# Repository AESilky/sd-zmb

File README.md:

# Silky Design & CMOS1 - Z80 Retro Motherboard

This is a Z80-based 'retro-style' Single Board Computer (motherboard).

The motherboard includes enough to run stand-alone.
That includes:

1. Z80 CPU
2. Selectable CPU clock frequencies
3. Reset circuit, divided into a POR board/system reset and a Z80/CPU only reset
4. Memory Management Unit (MMU) that provides bank selecting 8 of 64 8K banks (2M physical address)
5. 512K bytes RAM and 512K bytes Flash ROM
6. 2 Serial ports. One with USB 'device' interface, one with USB host interface (KBD)
7. RP2040 module to provide USB Host (for a keyboard) and an SD Card interface. The SD Card can be used for:
   a. EEPROM (like) configuration storage
   b. Virtual IDE drive(s)
   c. Raw SD Card access
   d. Multicolor LED indicator (via the onboard NeoPixel)
8. Programmable BAUD rate generator
9. Periodic interrupt generated by 3rd CTC channel
10. OLED or TFT graphics display (can be used for graphics or multi-line text)
11. RC2014-80 Extended/Enhanced Bus

The design started with much more on the board, but has been paired down to make the size and complexity of the board more reasonable. The 'features' that have been removed have been moved into projects of their own to be built-out as expansion boards.

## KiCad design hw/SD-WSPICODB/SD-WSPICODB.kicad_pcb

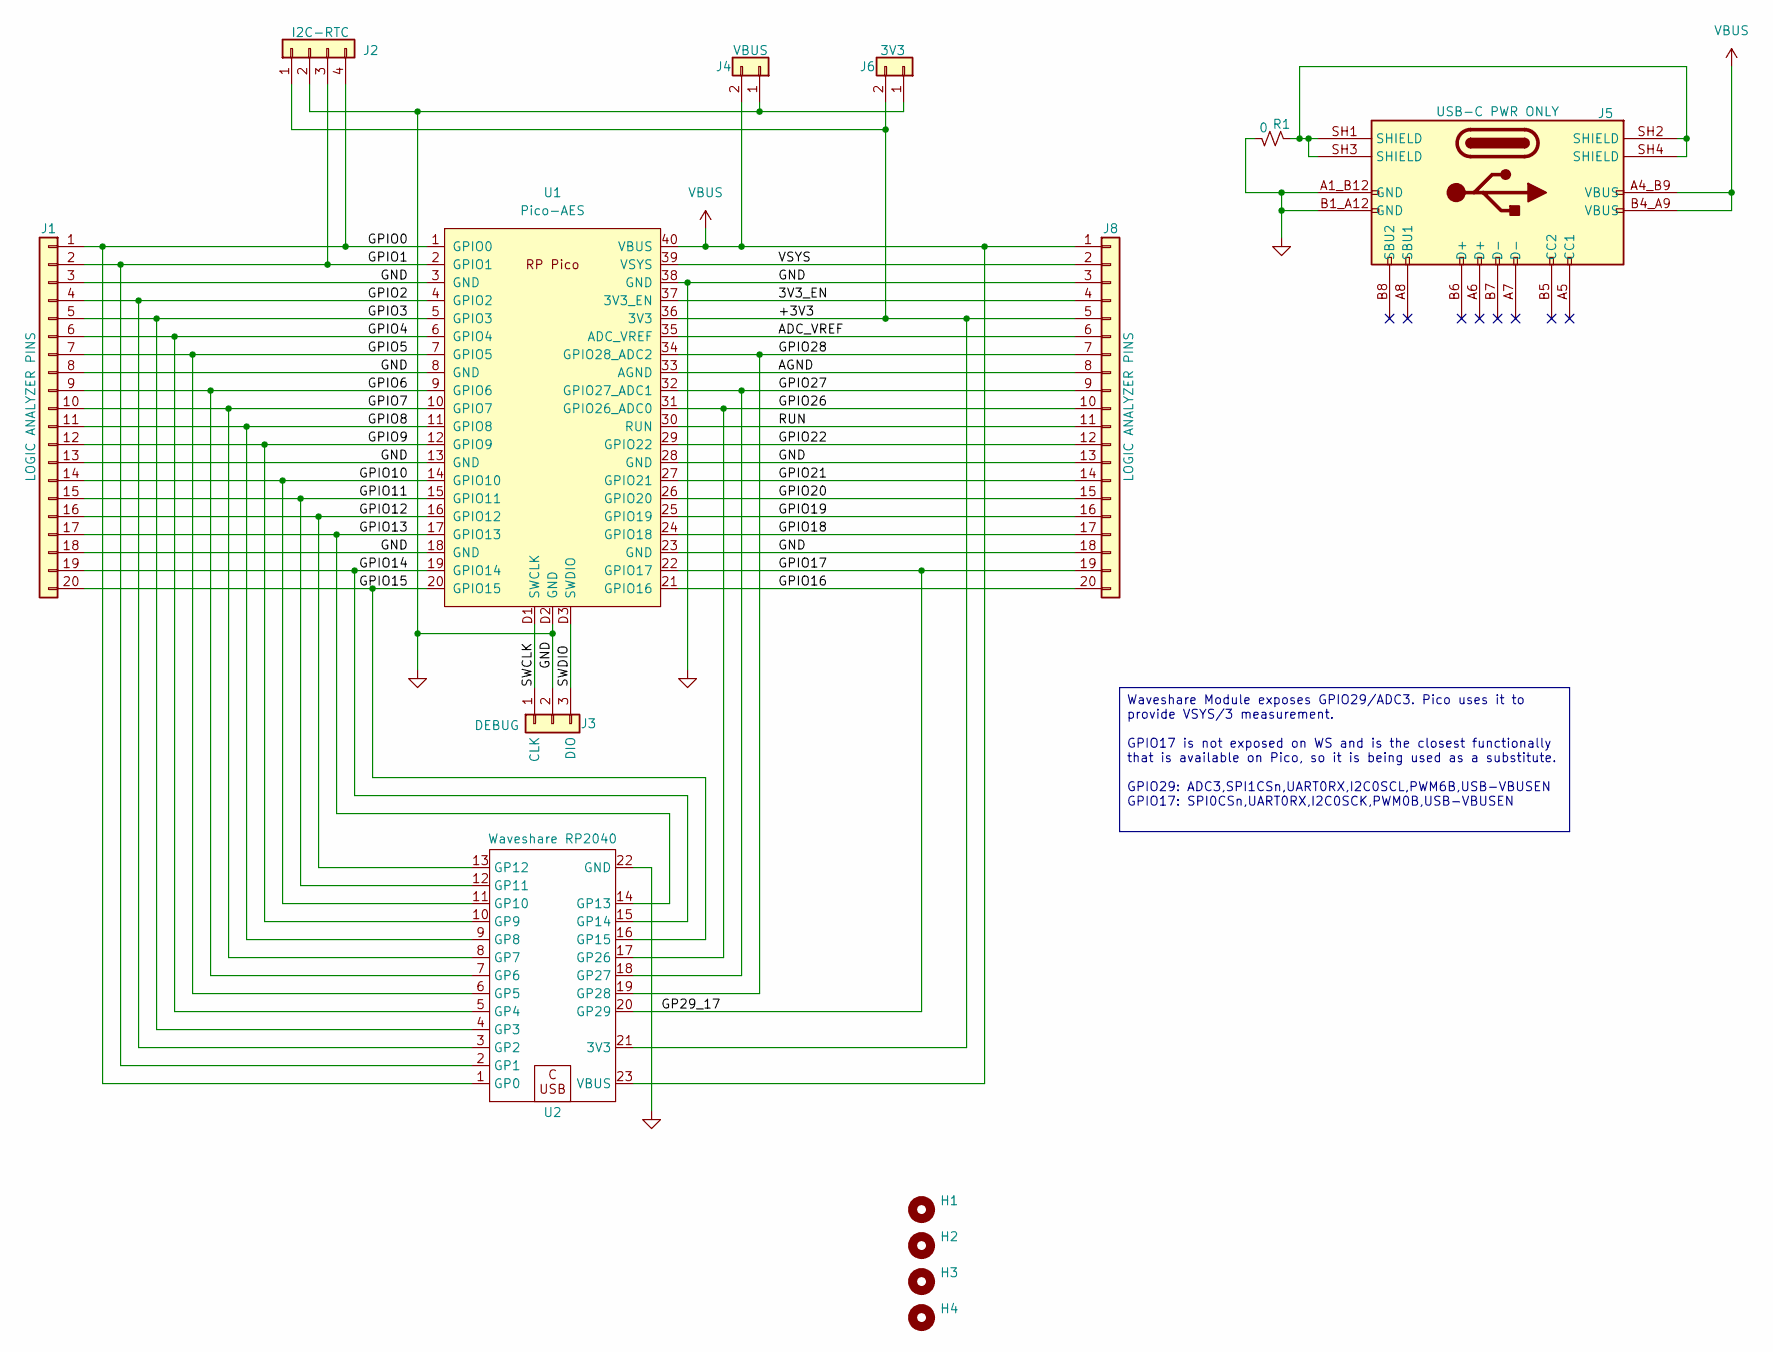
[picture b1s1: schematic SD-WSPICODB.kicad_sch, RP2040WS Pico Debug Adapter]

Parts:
H1, H2, H3, H4: MountingHole; MountingHole_2.2mm_M2
J1, J8: CONN 1x20 HDR; PinHeader_1x20_P2.54mm_Vertical
J2: HDR 1x04 Socket; PinSocket_1x04_P2.54mm_Vertical
J3: CONN 1x3 HDR; PinHeader_1x03_P2.54mm_Vertical
J4, J6: CONN 1x2 HDR; PinHeader_1x02_P2.54mm_Vertical
J5: USB-C PWR ONLY; AES-USB_C-Molex-BdTopMnt-2171790001
R1: 0; R_0805_2012Metric_Pad1.20x1.40mm_HandSolder
U1: Pico-AES; AES-RPi_Pico_SMD_TH
U2: Waveshare RP2040; RP2040_WS-AES

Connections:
/3V3_EN: J8.4, U1.37 (3V3_EN)
/+3V3: J2.1, J6.2, J8.5, U1.36 (3V3), U2.21 (3V3)
/ADC_VREF: J8.6, U1.35 (ADC_VREF)
/AGND: J8.8, U1.33 (AGND)
/GP29_17: J8.19, U1.22 (GPIO17), U2.20 (GP29)
/GPIO0: J1.1, J2.4, U1.1 (GPIO0), U2.1 (GP0)
/GPIO1: J1.2, J2.3, U1.2 (GPIO1), U2.2 (GP1)
/GPIO2: J1.4, U1.4 (GPIO2), U2.3 (GP2)
/GPIO3: J1.5, U1.5 (GPIO3), U2.4 (GP3)
/GPIO4: J1.6, U1.6 (GPIO4), U2.5 (GP4)
/GPIO5: J1.7, U1.7 (GPIO5), U2.6 (GP5)
/GPIO6: J1.9, U1.9 (GPIO6), U2.7 (GP6)
/GPIO7: J1.10, U1.10 (GPIO7), U2.8 (GP7)
/GPIO8: J1.11, U1.11 (GPIO8), U2.9 (GP8)
/GPIO9: J1.12, U1.12 (GPIO9), U2.10 (GP9)
/GPIO10: J1.14, U1.14 (GPIO10), U2.11 (GP10)
/GPIO11: J1.15, U1.15 (GPIO11), U2.12 (GP11)
/GPIO12: J1.16, U1.16 (GPIO12), U2.13 (GP12)
/GPIO13: J1.17, U1.17 (GPIO13), U2.14 (GP13)
/GPIO14: J1.19, U1.19 (GPIO14), U2.15 (GP14)
/GPIO15: J1.20, U1.20 (GPIO15), U2.16 (GP15)
/GPIO16: J8.20, U1.21 (GPIO16)
/GPIO18: J8.17, U1.24 (GPIO18)
/GPIO19: J8.16, U1.25 (GPIO19)
/GPIO20: J8.15, U1.26 (GPIO20)
/GPIO21: J8.14, U1.27 (GPIO21)
/GPIO22: J8.12, U1.29 (GPIO22)
/GPIO26: J8.10, U1.31 (GPIO26_ADC0), U2.17 (GP26)
/GPIO27: J8.9, U1.32 (GPIO27_ADC1), U2.18 (GP27)
/GPIO28: J8.7, U1.34 (GPIO28_ADC2), U2.19 (GP28)
/RUN: J8.11, U1.30 (RUN)
/SWCLK: J3.1, U1.D1 (SWCLK)
/SWDIO: J3.3, U1.D3 (SWDIO)
/VSYS: J8.2, U1.39 (VSYS)
GND: J1.3, J1.8, J1.13, J1.18, J2.2, J3.2, J4.1, J5.A1_B12 (GND), J5.B1_A12 (GND), J6.1, J8.3, J8.13, J8.18, R1.2, U1.3 (GND), U1.8 (GND), U1.13 (GND), U1.18 (GND), U1.23 (GND), U1.28 (GND), U1.38 (GND), U1.D2 (GND), U2.22 (GND)
unnamed: J5.SH1 (SHIELD), J5.SH2 (SHIELD), J5.SH3 (SHIELD), J5.SH4 (SHIELD), R1.1
VBUS: J4.2, J5.A4_B9 (VBUS), J5.B4_A9 (VBUS), J8.1, U1.40 (VBUS), U2.23 (VBUS)

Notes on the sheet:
Waveshare Module exposes GPIO29/ADC3. Pico uses it to provide VSYS/3 measurement. GPIO17 is not exposed on WS and is the closest functionally that is available on Pico, so it is being used as a substitute. GPIO29: ADC3,SPI1CSn,UART0RX,I2C0SCL,PWM6B,USB-VBUSEN GPIO17: SPI0CSn,UART0RX,I2C0SCK,PWM0B,U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

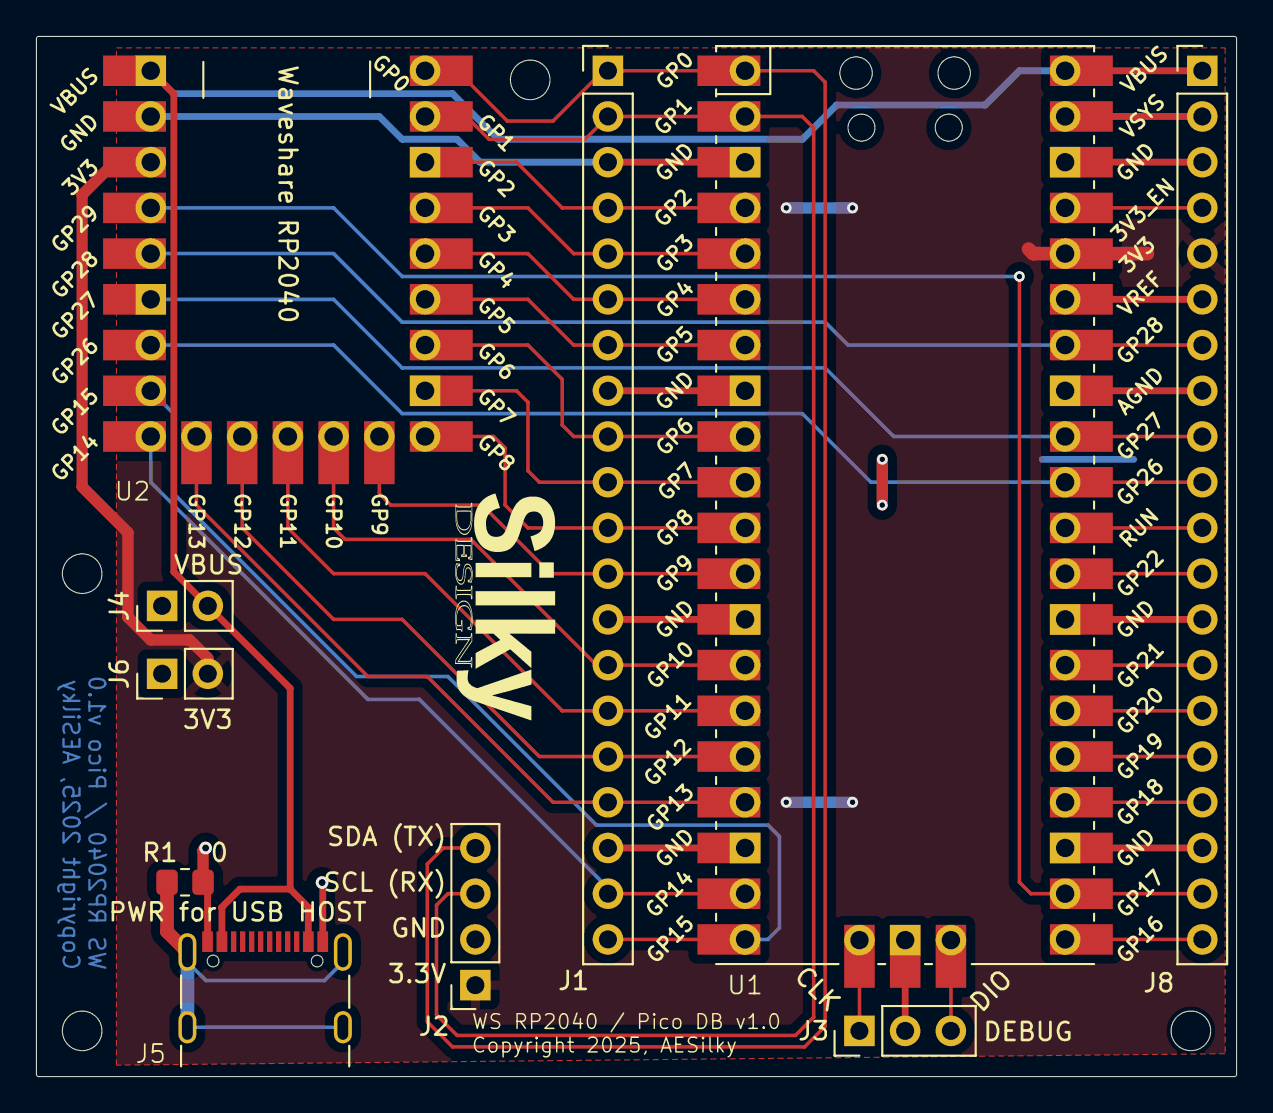
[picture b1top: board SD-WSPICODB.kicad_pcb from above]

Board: 2 copper layers, 66.7 x 57.8 mm, 14 parts (0 on the bottom side), 37 nets.

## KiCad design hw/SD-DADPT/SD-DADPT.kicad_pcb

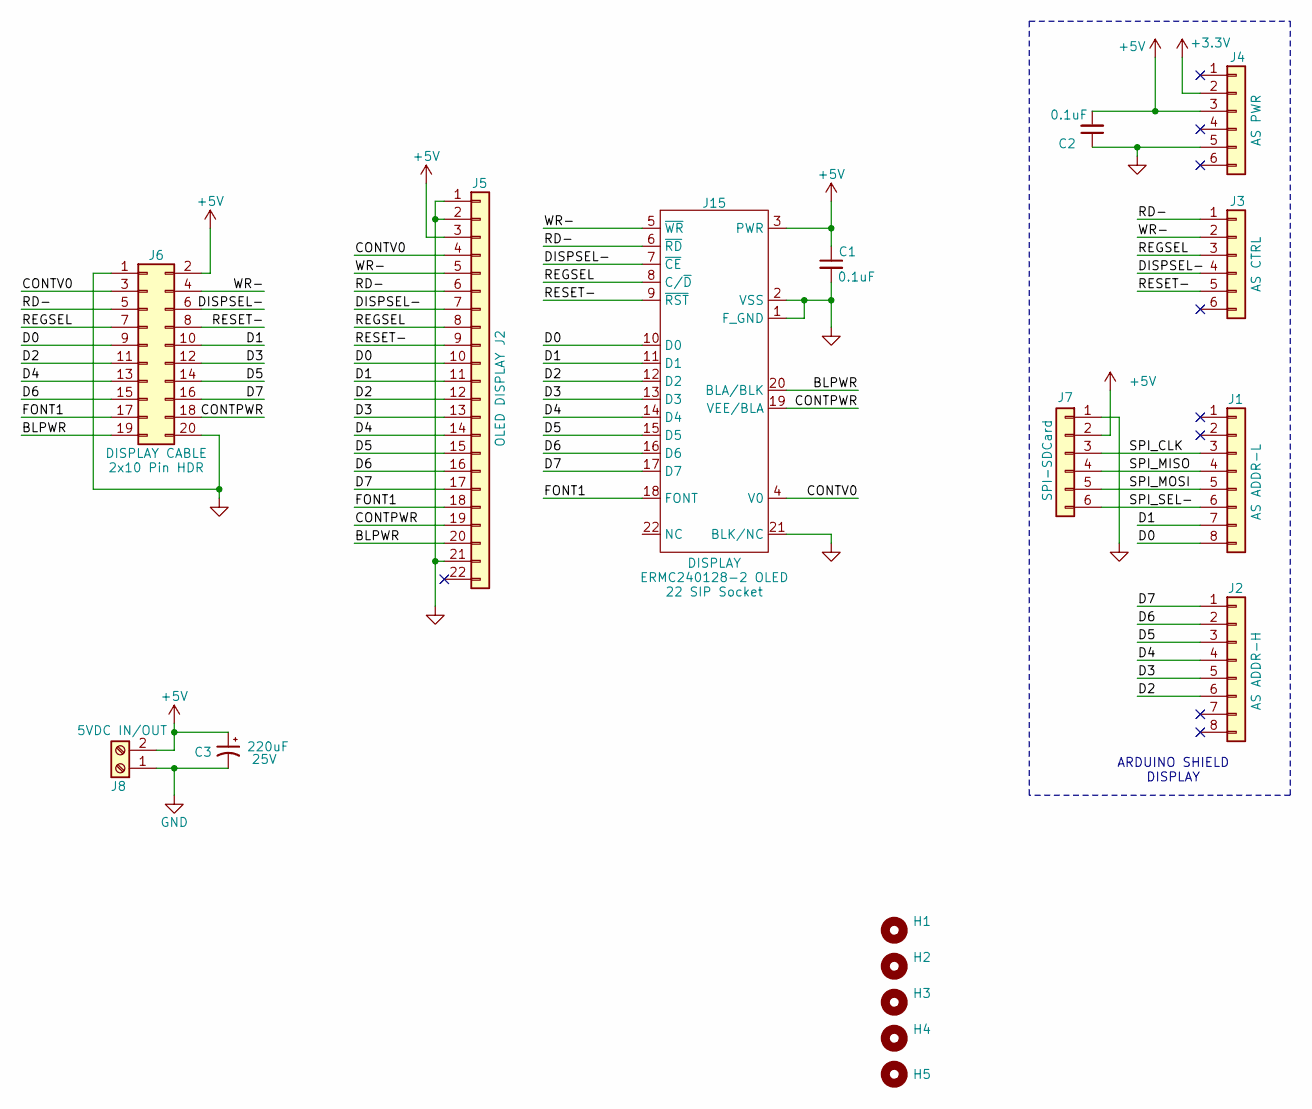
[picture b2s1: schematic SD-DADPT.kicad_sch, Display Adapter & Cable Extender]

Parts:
C1, C2: 0.1uF; C_0603_1608Metric_Pad1.08x0.95mm_HandSolder
C3: 220uF; CP_Radial_D6.3mm_P2.50mm; Voltage 25V
H1, H2, H3, H4, H5: MountingHole; MountingHole_3.2mm_M3
J1, J2: CONN 1x8 Socket; PinSocket_1x08_P2.54mm_Vertical
J3, J4: CONN 1x6 Socket; PinSocket_1x06_P2.54mm_Vertical
J5: CONN 1x22 SOCKET; PinSocket_1x22_P2.54mm_Vertical
J6: HDR 2x10 Pin; PinHeader_2x10_P2.54mm_Vertical; PartOpt1 2x10 Pin HDR
J7: CONN 1x6 HDR; PinHeader_1x06_P2.54mm_Vertical
J8: Screw_Terminal_01x02; AES-TermBlock-2POS-5mm-Horz
J15: DISPLAY; OLED-Disp-Socket-P2-8BitPI-AES; PartOpt1 22 SIP Socket

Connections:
+3.3V: J4.2
+5V: C1.1, C2.2, C3.1, J4.3, J5.3, J6.2, J7.2, J8.2, J15.3 (PWR)
/BLPWR: J5.20, J6.19, J15.20 (BLA/BLK)
/CONTPWR: J5.19, J6.18, J15.19 (VEE/BLA)
/CONTV0: J5.4, J6.3, J15.4 (V0)
/D0: J1.8, J5.10, J6.9, J15.10 (D0)
/D1: J1.7, J5.11, J6.10, J15.11 (D1)
/D2: J2.6, J5.12, J6.11, J15.12 (D2)
/D3: J2.5, J5.13, J6.12, J15.13 (D3)
/D4: J2.4, J5.14, J6.13, J15.14 (D4)
/D5: J2.3, J5.15, J6.14, J15.15 (D5)
/D6: J2.2, J5.16, J6.15, J15.16 (D6)
/D7: J2.1, J5.17, J6.16, J15.17 (D7)
/DISPSEL-: J3.4, J5.7, J6.6, J15.7 (~CE)
/FONT1: J5.18, J6.17, J15.18 (FONT)
/RD-: J3.1, J5.6, J6.5, J15.6 (~RD)
/REGSEL: J3.3, J5.8, J6.7, J15.8 (C/~D)
/RESET-: J3.5, J5.9, J6.8, J15.9 (~RST)
/SPI_CLK: J1.3, J7.3
/SPI_MISO: J1.4, J7.4
/SPI_MOSI: J1.5, J7.5
/SPI_SEL-: J1.6, J7.6
/WR-: J3.2, J5.5, J6.4, J15.5 (~WR)
GND: C1.2, C2.1, C3.2, J4.5, J5.1, J5.2, J5.21, J6.1, J6.20, J7.1, J8.1, J15.1 (F_GND), J15.2 (VSS), J15.21 (BLK/NC)

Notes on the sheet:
ARDUINO SHIELD DISPLAY

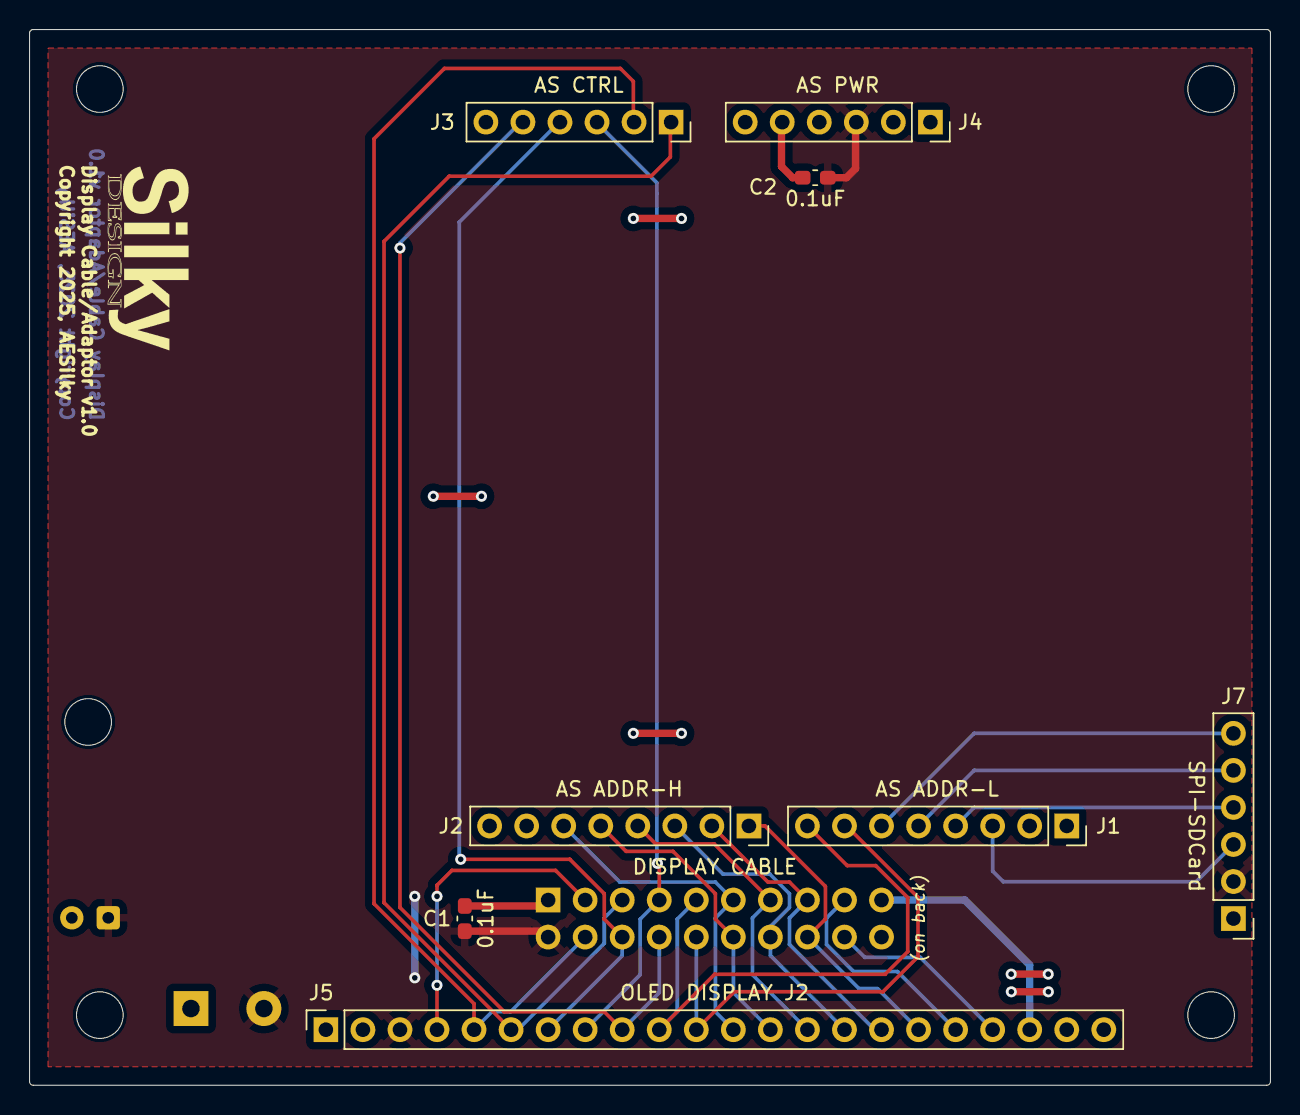
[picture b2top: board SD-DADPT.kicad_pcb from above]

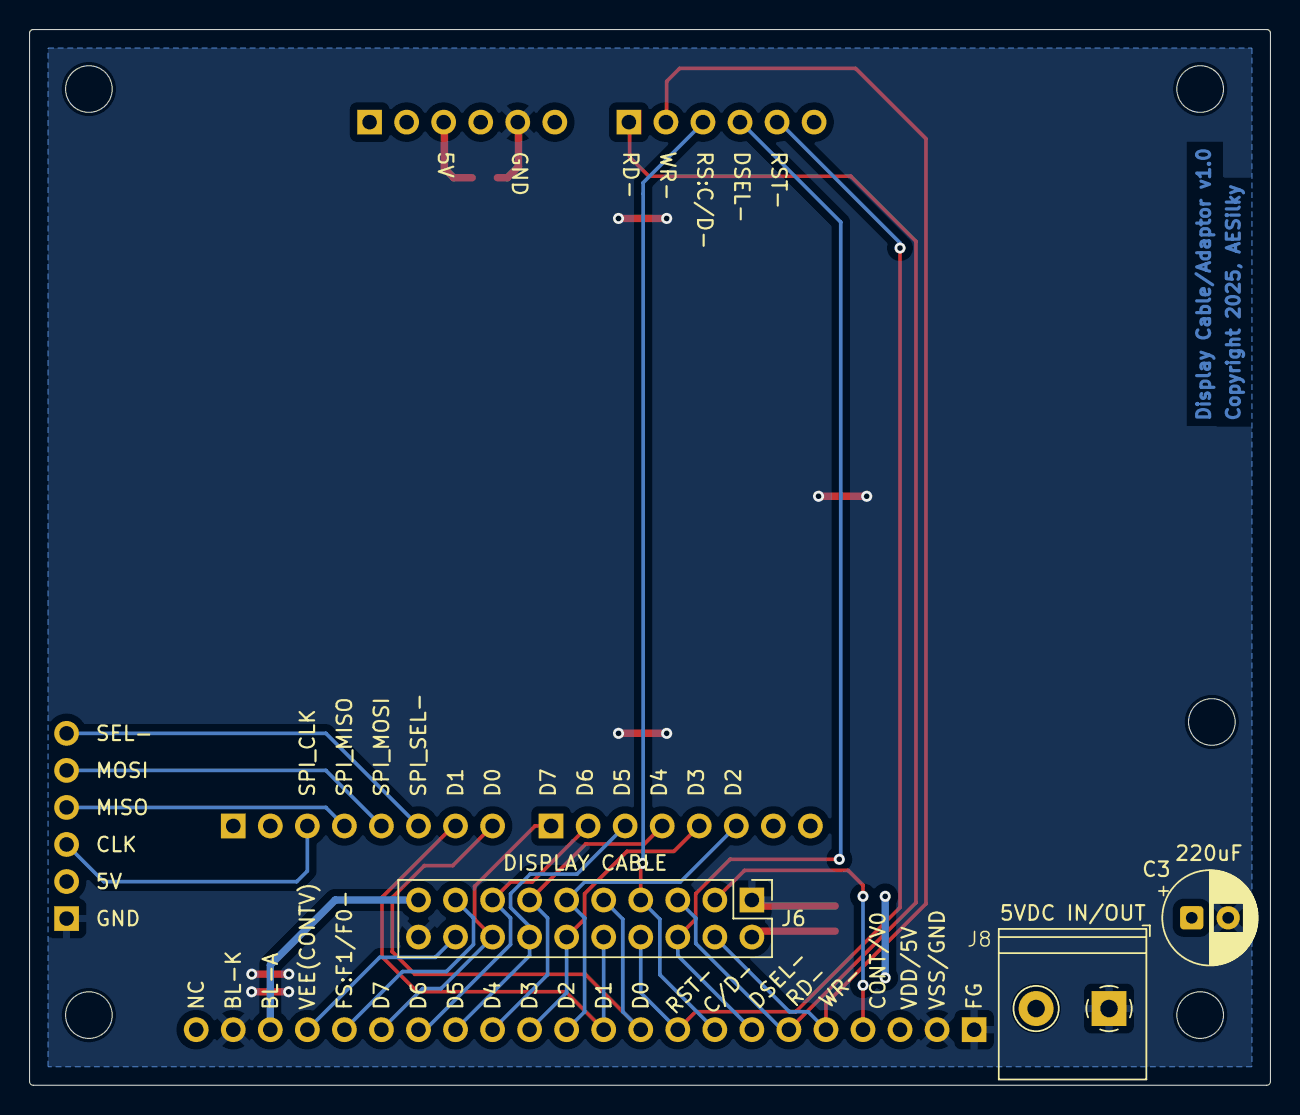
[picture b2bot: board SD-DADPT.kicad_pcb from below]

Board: 2 copper layers, 85.1 x 72.4 mm, 16 parts (3 on the bottom side), 23 nets.

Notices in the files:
hw/SD-DADPT/SD-DADPT.kicad_pcb:
Copyright 2025 AESilky
hw/SD-ZMB/SD-ZMB.kicad_pcb:
Copyright 2025 AESilky & SmM
